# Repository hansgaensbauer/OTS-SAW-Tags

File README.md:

# OTS SAW Tags
Passive SAW tags using cheap, off-the-shelf SAW filters.

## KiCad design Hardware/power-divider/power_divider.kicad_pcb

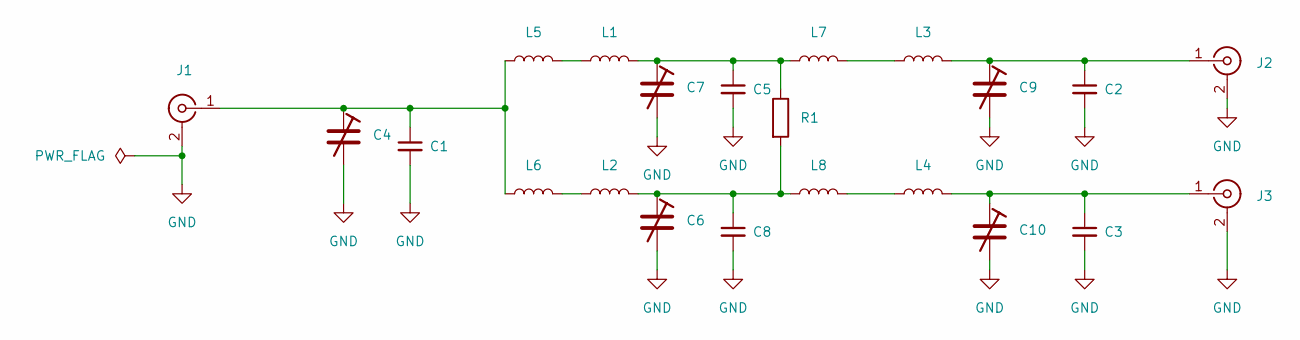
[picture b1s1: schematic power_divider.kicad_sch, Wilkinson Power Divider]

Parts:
C1, C2, C3, C5, C8: C_Small; C_0603_1608Metric
C4, C7, C9, C10: C_Trim; C_Trimmer_Sprague-Goodman_SGC3
C6: v; C_Trimmer_Sprague-Goodman_SGC3
J1, J2, J3: Conn_Coaxial; SMA_Samtec_SMA-J-P-X-ST-EM1_EdgeMount
L1, L2, L3, L4, L5, L6, L7, L8: L; L_0603_1608Metric
R1: R; R_0603_1608Metric

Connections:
GND: C1.2, C2.2, C3.2, C4.2, C5.2, C6.2, C7.2, C8.2, C9.2, C10.2, J1.2 (Ext), J2.2 (Ext), J3.2 (Ext)
unnamed: C1.1, C4.1, J1.1 (In), L5.1, L6.1
unnamed: C2.1, C9.1, J2.1 (In), L3.2
unnamed: C5.1, C7.1, L1.2, L7.1, R1.1
unnamed: C6.1, C8.1, L2.2, L8.1, R1.2
unnamed: C3.1, C10.1, J3.1 (In), L4.2
unnamed: L1.1, L5.2
unnamed: L2.1, L6.2
unnamed: L3.1, L7.2
unnamed: L4.1, L8.2

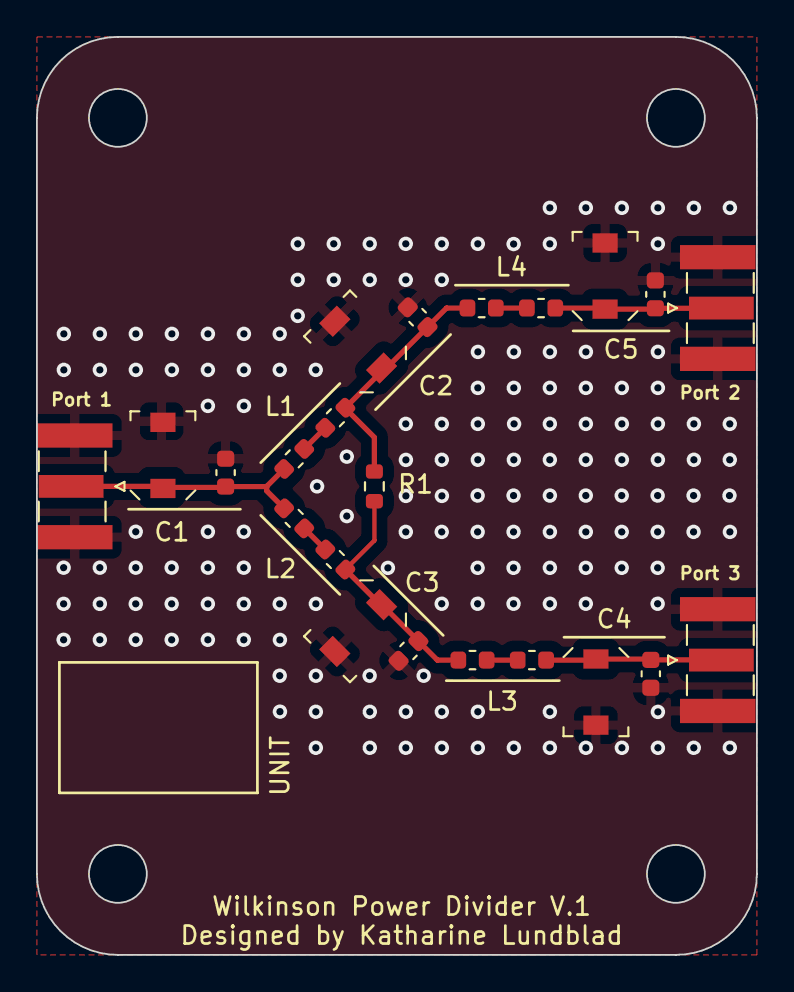
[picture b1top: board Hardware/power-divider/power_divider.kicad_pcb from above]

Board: 4 copper layers, 40.0 x 51.0 mm, 22 parts (0 on the bottom side), 10 nets.

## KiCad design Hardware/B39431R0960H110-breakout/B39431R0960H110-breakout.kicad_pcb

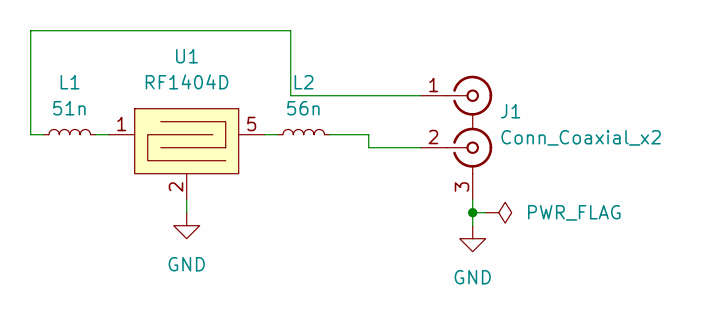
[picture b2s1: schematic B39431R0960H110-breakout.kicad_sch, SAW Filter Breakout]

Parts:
J1: Conn_Coaxial_x2; SMA-KIT-1.5MF
L1: 51n; L_0402_1005Metric
L2: 56n; L_0402_1005Metric
U1: RF1404D

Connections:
GND: J1.3 (EXT), U1.2, U1.3, U1.4, U1.6, U1.7, U1.8
unnamed: J1.1 (IN1), L1.1
unnamed: J1.2 (IN2), L2.2
unnamed: L1.2, U1.1
unnamed: L2.1, U1.5

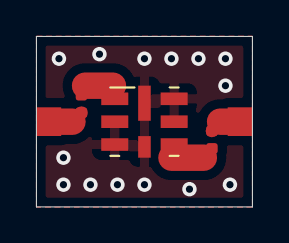
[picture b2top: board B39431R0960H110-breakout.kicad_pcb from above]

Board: 2 copper layers, 12.0 x 9.5 mm, 4 parts (0 on the bottom side), 5 nets.

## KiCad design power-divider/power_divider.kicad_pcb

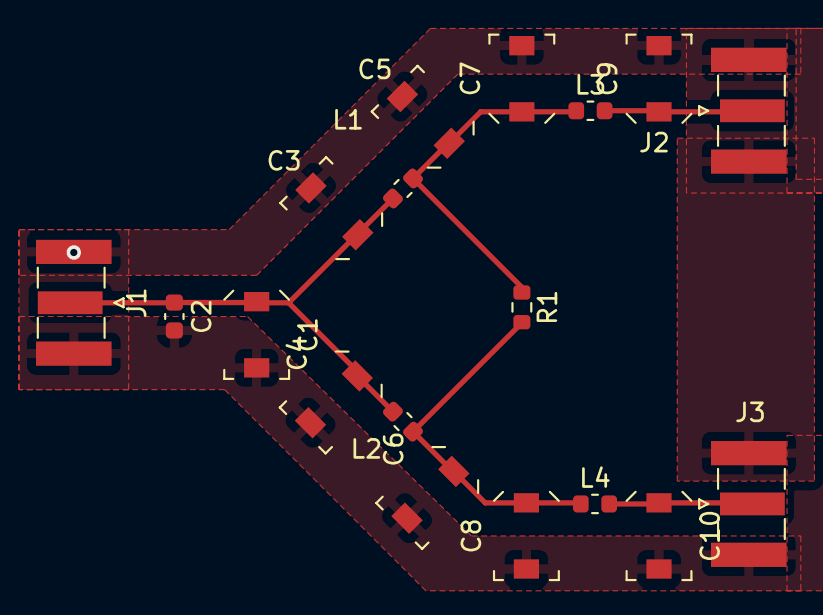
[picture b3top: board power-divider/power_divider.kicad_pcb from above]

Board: 2 copper layers, 18 parts (0 on the bottom side), 6 nets.

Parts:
C1, C3, C4, C5, C6, C7, C8, C9, C10: C_Trim; C_Trimmer_Sprague-Goodman_SGC3
C2: C; C_0603_1608Metric
J1, J2, J3: Conn_Coaxial_Power; SMA_Samtec_SMA-J-P-X-ST-EM1_EdgeMount
L1, L2, L3, L4: L; L_0603_1608Metric
R1: R; R_0603_1608Metric

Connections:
GND: C1.2, C2.2, C3.2, C4.2, C5.2, C6.2, C7.2, C8.2, C9.2, C10.2, J1.2 (Ext), J2.2 (Ext), J3.2 (Ext)
unnamed: C1.1, C2.1, C3.1, C4.1, J1.1 (In), L1.1, L2.1
unnamed: C6.1, C8.1, L2.2, L4.1, R1.2
unnamed: C9.1, J2.1 (In), L3.2
unnamed: C10.1, J3.1 (In), L4.2
unnamed: C5.1, C7.1, L1.2, L3.1, R1.1

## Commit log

2022-07-02 Project: Add Hardware Folders
    Also add some parts for use in a SAW breakout.
2022-07-02 B3943 Breakout: Add design files.
    ERC/DRC Fail
2022-07-02 B39431: Don't track backups
2022-07-02 SAW Breakout: DRC ERC Pass
    Ready for PR
2022-07-02 Calculator: Add files
2022-07-02 Add diagram to README
2022-07-02 fixed path
2022-07-02 Fixed zones, added edgecuts and vias
2022-07-02 Working Tag Calculator
2022-07-03 Calculator: Remove magic numbers
2022-07-03 Revert "Power divider"
2022-07-04 Fix image link
    The image was broken after tag calculator was merged.
2022-07-07 See wilsonian PR, changed schematic and board
2022-07-07 Hans's gargantuine PR review has been fulfilled except for rebasing, removed unwanted sch file and README.md
2022-07-07 Added schematic to path
2022-07-07 Vias galore
2022-07-07 Made words bigger
2022-07-07 Committing the same conflicting file for some reason
2022-07-07 Fixing merge conflict in 7a0004a commit
2022-07-07 Revert "Fixing merge conflict in 7a0004a commit"
    This reverts commit 6070d036bfbb01e51238e389a7ff300d217176a7.
2022-07-07 Revert "Committing the same conflicting file for some reason"
    This reverts commit 15b06b98800503f49b9114d44c60aae0cede40bb.
2022-07-07 New project
2022-07-07 PD: Silkscreen Color Tweak
    - Changed bottom silkscreen to green
    - Aligned board edges and fill polygon to grid
    - Rounded the corners
    - Added box for label
    - Moved R1 slightly closer
    - Increased default netclass clearance from 0.2 to 0.6mm
2022-07-08 Plotting and Drill Files
